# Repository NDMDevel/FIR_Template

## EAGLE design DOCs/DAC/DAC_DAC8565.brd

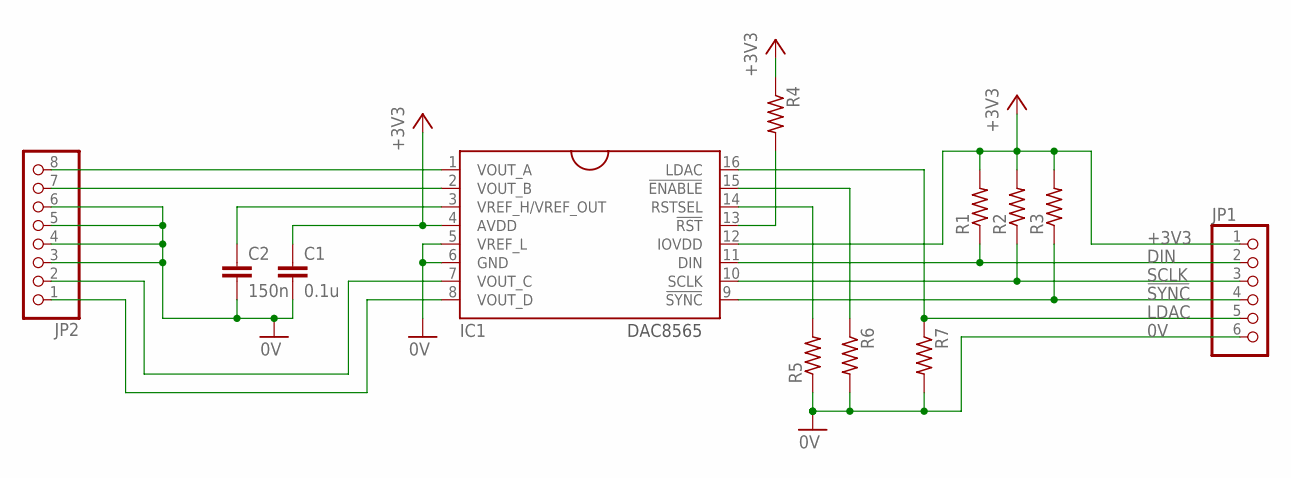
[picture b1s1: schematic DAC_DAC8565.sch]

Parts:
C1: 0.1u; C1206
C2: 150n; C1206
IC1: DAC8565; TSSOP-16
JP1: PINHD-1X6; 1X06
JP2: PINHD-1X8; 1X08
R1, R2, R3, R4, R5, R7: R-US_R0805; R0805
R6: R-US_0204/7; 0204/7

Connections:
0V: C1.2, C2.2, IC1.5 (VREF_L), IC1.6 (GND), JP1.6, JP2.3, JP2.4, JP2.5, JP2.6, R5.1, R6.2, R7.2
!SYNC!: IC1.9 (!SYNC!), JP1.4, R3.1
+3V3: C1.1, IC1.4 (AVDD), IC1.12 (IOVDD), JP1.1, R1.2, R2.2, R3.2, R4.1
DIN: IC1.11 (DIN), JP1.2, R1.1
LDAC: IC1.16 (LDAC), JP1.5, R7.1
unnamed: IC1.13 (!RST!), R4.2
unnamed: IC1.14 (RSTSEL), R5.2
unnamed: IC1.1 (VOUT_A), JP2.8
unnamed: C2.1, IC1.3 (VREF_H/VREF_OUT)
unnamed: IC1.15 (!ENABLE!), R6.1
OUT_B: IC1.2 (VOUT_B), JP2.7
OUT_C: IC1.7 (VOUT_C), JP2.2
OUT_D: IC1.8 (VOUT_D), JP2.1
SCLK: IC1.10 (SCLK), JP1.3, R2.1

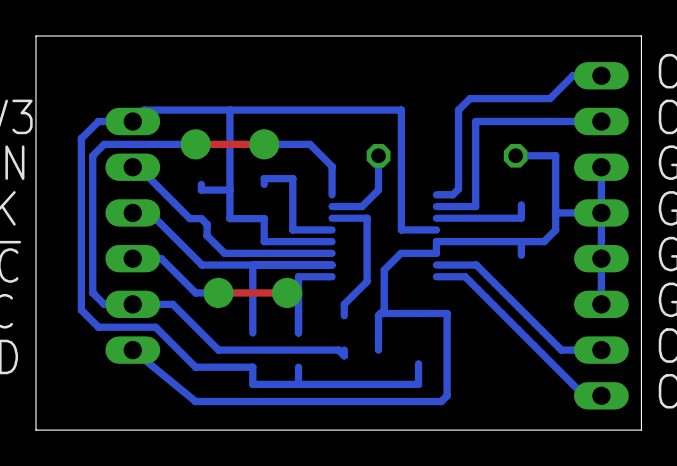
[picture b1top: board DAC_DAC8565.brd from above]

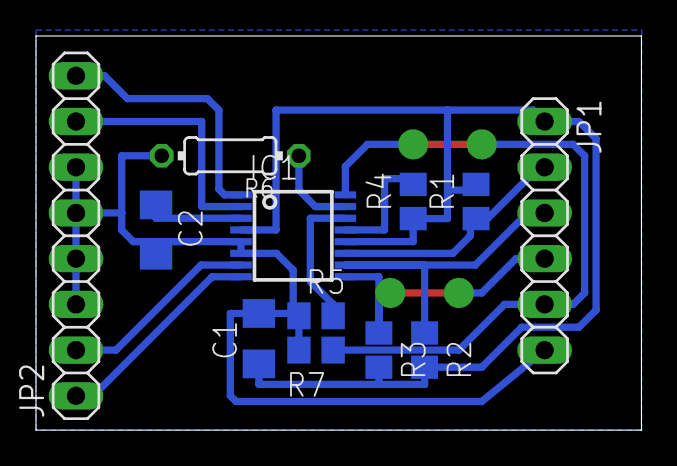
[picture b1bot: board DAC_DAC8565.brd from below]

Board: 2 copper layers, 33.6 x 21.9 mm, 12 parts (12 on the bottom side), 14 nets.

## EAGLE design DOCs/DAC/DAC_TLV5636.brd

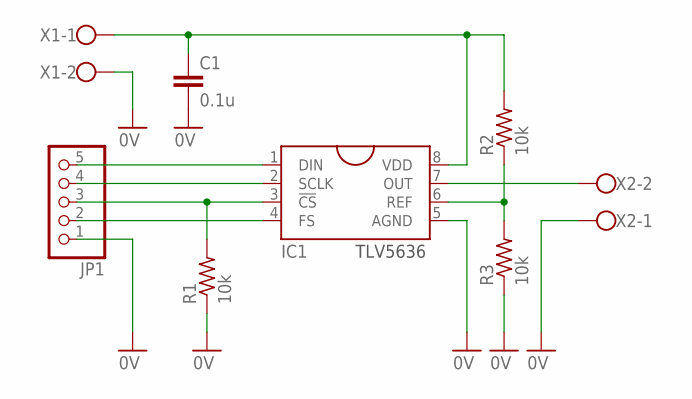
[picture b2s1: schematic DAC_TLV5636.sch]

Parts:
C1: 0.1u; C1206
IC1: TLV5636; SOIC8
JP1: PINHD-1X5; 1X05
R1, R2, R3: 10k; R0805
X1, X2: W237-102

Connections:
0V: C1.2, IC1.5 (AGND), JP1.1, R1.1, R3.1, X1.2, X2.1
unnamed: IC1.4 (FS), JP1.2
unnamed: IC1.3 (!CS!), JP1.3, R1.2
unnamed: IC1.2 (SCLK), JP1.4
unnamed: IC1.1 (DIN), JP1.5
unnamed: IC1.6 (REF), R2.1, R3.2
unnamed: C1.1, IC1.8 (VDD), R2.2, X1.1
unnamed: IC1.7 (OUT), X2.2

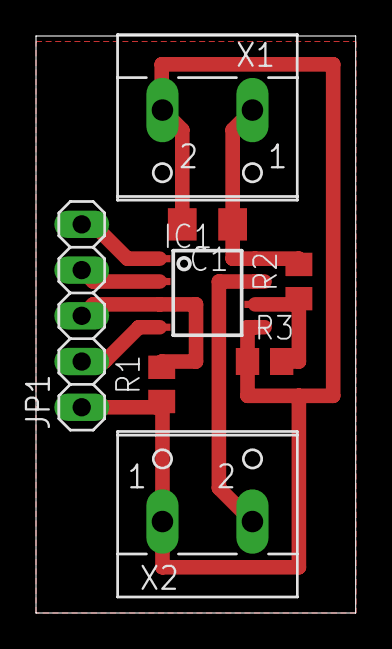
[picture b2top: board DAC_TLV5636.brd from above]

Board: 2 copper layers, 17.8 x 32.1 mm, 8 parts (0 on the bottom side), 8 nets.

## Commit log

2017-05-29 Primer Commit. FIR orden 64 funcionando con fs = 76923 Hz. Documentacion y proyecto EAGLE del DAC disponibles.
2017-05-29 Se agrega libro digital Shenoi (para filtros digitales y realizacion). Se incluye el script "generate_filter.m" que funciona como "fir2" pero el orden es fijo en 64, produce graficas y genera los coe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
